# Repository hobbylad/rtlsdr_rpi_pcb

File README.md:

# rtlsdr_rpi_pcb

##RTL-SDR and Raspberry Pi 3 Carrier PCB 

An RTL-SDR and Raspberry Pi make a good combination. The RTL-SDR has a range of 24MHz-1.7GHz and the RPi 3 enough power to compile and run a wide range of open-source receiver software.

The aim of this carrier PCB is to mechanically combine both SDR and RPi, reduce wiring, allow the control of external devices such as relays and provide power with some expansion capability. Safety, noise and RPI cooling were also considerations.

The board was designed with Kicad on a single-sided board with the aim of keeping the PCB as simple as possible for hobbyists to construct with chemical etching or a milling machine.

See the [blog page for this project](https://hobbylad.wordpress.com/2021/06/17/rtl-sdr-raspberry-pi-carrier-pcb/).

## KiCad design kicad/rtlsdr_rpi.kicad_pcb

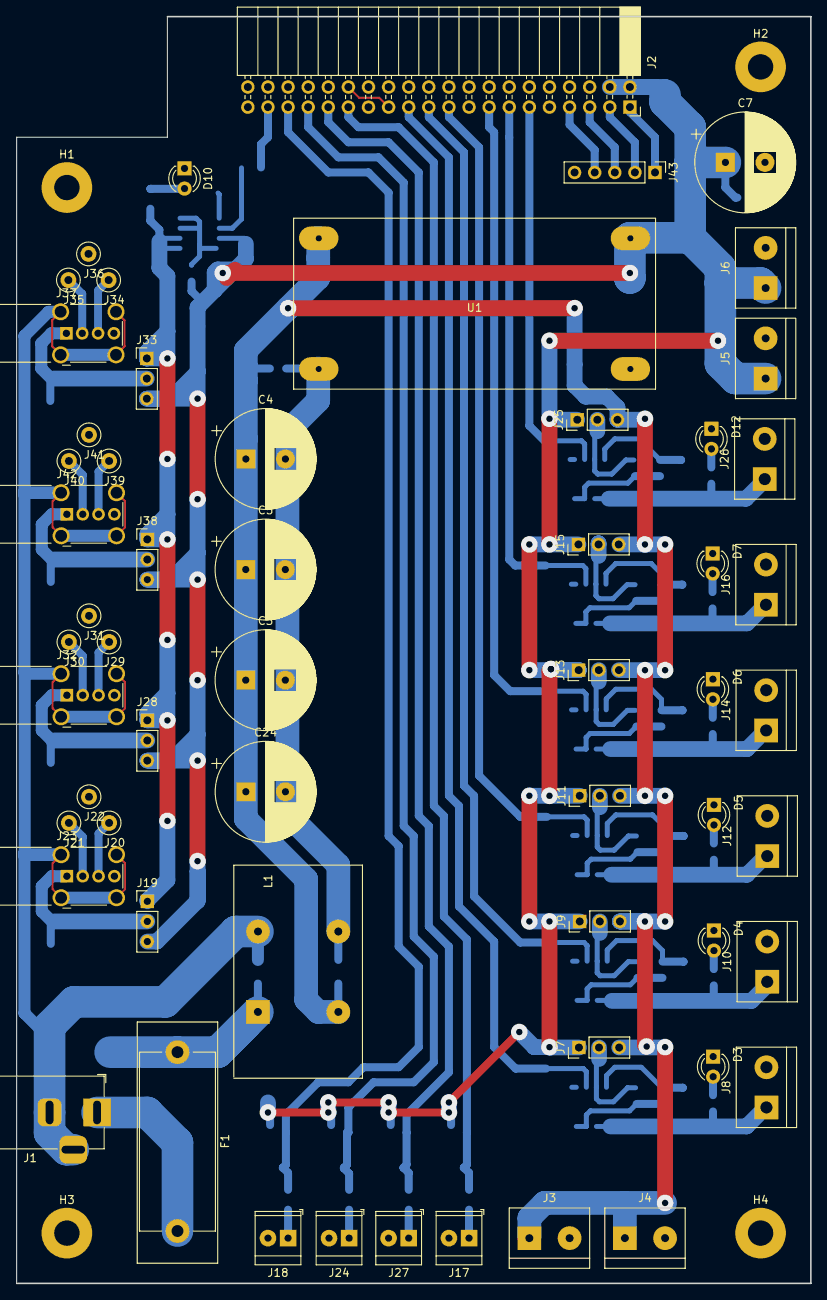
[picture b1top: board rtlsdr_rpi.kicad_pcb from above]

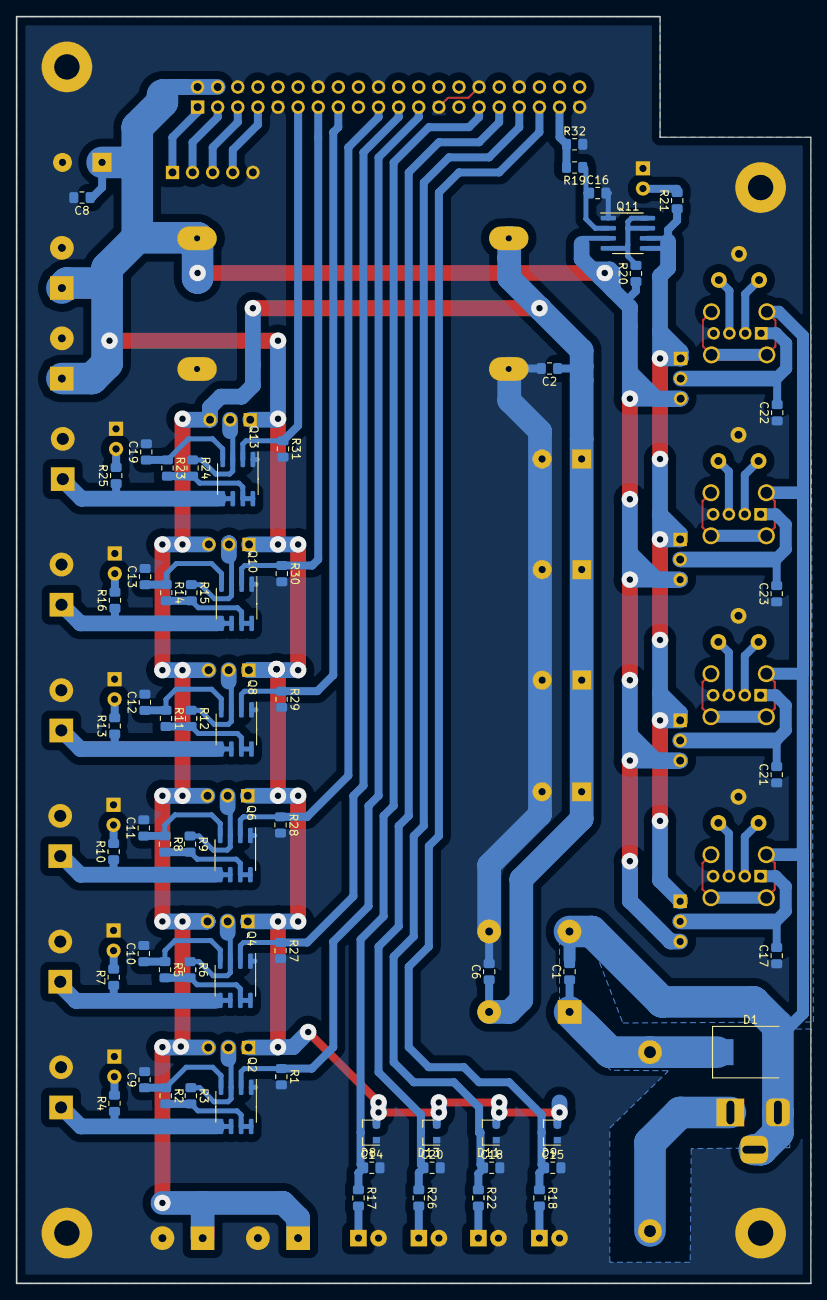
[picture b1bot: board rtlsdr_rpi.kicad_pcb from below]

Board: 2 copper layers, 100.3 x 160.0 mm, 125 parts (63 on the bottom side), 71 nets.

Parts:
C1, C2, C6, C8, C9, C10, C11, C12, C13, C14, C15, C16, C17, C18, C19, C20, C21, C22, C23: 100n; C_0805_2012Metric_Pad1.15x1.40mm_HandSolder
C3, C4, C5, C24: 1000u; CP_Radial_D12.5mm_P5.00mm
C7: 3300u; CP_Radial_D12.5mm_P5.00mm
D1: MBRS540T3G; D_SMC
D3, D4, D5, D6, D7, D12: LED; LED_D3.0mm
D8, D9, D11, D13: BAT54S; SOT-23
D10: GREEN; LED_D3.0mm
F1: Fuse; Fuseholder_Cylinder-5x20mm_Stelvio-Kontek_PTF78_Horizontal_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
H1, H2, H3, H4: MountingHole_Pad; MountingHole_3.2mm_M3_Pad
J1: Barrel_Jack_Switch; BarrelJack_Horizontal
J2: Raspberry_Pi_2_3; PinSocket_2x20_P2.54mm_Horizontal
J3, J4, J5, J6, J8, J10, J12, J14, J16, J26: 01x02; TerminalBlock_bornier-2_P5.08mm
J7, J9, J11, J13, J15, J19, J25, J28, J33, J38: Conn_01x03; PinHeader_1x03_P2.54mm_Vertical
J17, J18, J24, J27: 01x02; TerminalBlock_TE_282834-2_1x02_P2.54mm_Horizontal
J20, J21, J22, J29, J30, J31, J34, J35, J36, J39, J40, J41: Conn_01x01; TestPoint_Loop_D2.50mm_Drill1.0mm_LowProfile
J23, J32, J37, J42: USB_A; USB_A_Wuerth_614004134726_Horizontal
J43: Conn_01x05_Male; PinHeader_1x05_P2.54mm_Vertical
L1: ?; L_CommonMode_Toroid_Vertical_L26mm_W12mm_Px10mm_Py10mm_Ebay
Q2, Q4, Q6, Q8, Q10, Q11, Q13: FDS8858CZ; SOIC-8_3.9x4.9mm_P1.27mm
R1, R2, R3, R5, R6, R8, R9, R11, R12, R14, R15, R17, R18, R19, R20, R22, R23, R24, R26, R27, R28, R29, R30, R31, R32: 10k; R_0805_2012Metric_Pad1.15x1.40mm_HandSolder
R4, R7, R10, R13, R16, R21, R25: 1k; R_0805_2012Metric_Pad1.15x1.40mm_HandSolder
U1: XL4015; XL4015_Converter

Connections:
5V2: C7.1, C8.1, D8.2, D9.2, D11.2, D13.2, J2.2, J2.4, J5.1, J6.1, J7.1, J9.1, J11.1, J13.1, J15.1, J19.3, J25.1, J28.3, J33.3, J38.3, Q11.3, R20.1, U1.3
12V: C2.1, C3.1, C4.1, C5.1, C6.1, J3.1, J4.1, J7.3, J9.3, J11.3, J13.3, J15.3, J25.3, L1.4, U1.1
/3V3: J2.1, J43.1
/EN_USB1: J2.37, R19.2, R32.1
/GPIO4: J2.7, J43.4
/IN1: C15.1, D9.3, J2.35, R18.1
/IN2: C18.1, D11.3, J2.33, R22.1
/IN3: C20.1, D13.3, J2.31, R26.1
/IN4: C14.1, D8.3, J2.29, R17.1
/OUT1: J2.11, Q13.2, R31.1
/OUT2: J2.13, Q10.2, R30.1
/OUT3: J2.15, Q8.2, R29.1
/OUT4: J2.19, Q6.2, R28.1
/OUT5: J2.21, Q4.2, R27.1
/OUT6: J2.23, Q2.2, R1.1
/SCL: J2.5, J43.3
/SDA: J2.3, J43.2
GND: C2.2, C3.2, C4.2, C5.2, C6.2, C7.2, C8.2, C9.2, C10.2, C11.2, C12.2, C13.2, C14.2, C15.2, C16.2, C17.1, C18.2, C19.2, C20.2, C21.1, C22.1, C23.1, C24.2, D3.1, D4.1, D5.1, D6.1, D7.1, D8.1, D9.1, D10.1, D11.1, D12.1, D13.1, H1.1, H2.1, H3.1, H4.1, J2.6, J2.9, J2.14, J2.20, J2.25, J2.30, J2.34, J2.39, J3.2, J4.2, J5.2, J6.2, J8.2, J10.2, J12.2, J14.2, J16.2, J17.2, J18.2, J22.1, J23.4, J24.2, J26.2, J27.2, J31.1, J32.4, J36.1, J37.4, J41.1, J42.4, J43.5, L1.3, Q2.1, Q4.1, Q6.1, Q8.1, Q10.1, Q11.1, Q13.1, R1.2, R27.2, R28.2, R29.2, R30.2, R31.2, R32.2, U1.2, U1.4
GNDREF: C1.2, D1.2, J1.2, J1.3, J23.5, J32.5, J37.5, J42.5, L1.2
unnamed: C1.1, D1.1, F1.1, L1.1
unnamed: C9.1, Q2.4, R2.1
unnamed: C10.1, Q4.4, R5.1
unnamed: C11.1, Q6.4, R8.1
unnamed: C12.1, Q8.4, R11.1
unnamed: C13.1, Q10.4, R14.1
unnamed: C16.1, Q11.2, R19.1
unnamed: C17.2, J19.2, J23.1
unnamed: C19.1, Q13.4, R23.1
unnamed: C21.2, J28.2, J32.1
unnamed: C22.2, J33.2, J37.1
unnamed: C23.2, J38.2, J42.1
unnamed: D3.2, R4.2
unnamed: D4.2, R7.2
unnamed: D5.2, R10.2
unnamed: D6.2, R13.2
unnamed: D7.2, R16.2
unnamed: D10.2, R21.2
unnamed: D12.2, R25.2
unnamed: F1.2, J1.1
unnamed: J7.2, Q2.3, R3.1
unnamed: J8.1, Q2.5, Q2.6, R4.1
unnamed: J9.2, Q4.3, R6.1
unnamed: J10.1, Q4.5, Q4.6, R7.1
unnamed: J11.2, Q6.3, R9.1
unnamed: J12.1, Q6.5, Q6.6, R10.1
unnamed: J13.2, Q8.3, R12.1
unnamed: J14.1, Q8.5, Q8.6, R13.1
unnamed: J15.2, Q10.3, R15.1
unnamed: J16.1, Q10.5, Q10.6, R16.1
unnamed: J17.1, R17.2
unnamed: J18.1, R18.2
unnamed: J20.1, J23.3
unnamed: J21.1, J23.2
unnamed: J24.1, R22.2
unnamed: J25.2, Q13.3, R24.1
unnamed: J26.1, Q13.5, Q13.6, R25.1
unnamed: J27.1, R26.2
unnamed: J29.1, J32.3
unnamed: J30.1, J32.2
unnamed: J34.1, J37.3
unnamed: J35.1, J37.2
unnamed: J39.1, J42.3
unnamed: J40.1, J42.2
unnamed: Q2.7, Q2.8, R2.2, R3.2
unnamed: Q4.7, Q4.8, R5.2, R6.2
unnamed: Q6.7, Q6.8, R8.2, R9.2
unnamed: Q8.7, Q8.8, R11.2, R12.2
unnamed: Q10.7, Q10.8, R14.2, R15.2
unnamed: Q11.4, Q11.7, Q11.8, R20.2
unnamed: Q13.7, Q13.8, R23.2, R24.2
SW_5V2: J19.1, J28.1, J33.1, J38.1, Q11.5, Q11.6, R21.1

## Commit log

2021-06-07 Initial schematic and layout.
2021-06-19 Added schmetic and layout drawing of prototype board.
2021-06-19 Create README.md
    Initial description.
